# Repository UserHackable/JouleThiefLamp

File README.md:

## Steam Punk Joule Thief Flashlight Project

This is another one of my Cache Makers 4H projects. 

We used a ferrite core to wind a small transformer, an LED, a 2N3904 Transistor and a resistor to make a tiny boost circuit regulated only by the knee voltage of the LED. 

I designed the circuit board to be snapped in half, and sandwich the transformer. The whole thing was then put into a 1/2 inch copper pipe union, with a couple inches of copper pipe and a cap for a case. 

## JouleThiefLamp 

### Board dimensions

* (119996, 60000) original units
* (1.2000, 0.6000) inches
* (30.4790, 15.2400) mm

| Front | Back |
| --- | --- |
|  |  |

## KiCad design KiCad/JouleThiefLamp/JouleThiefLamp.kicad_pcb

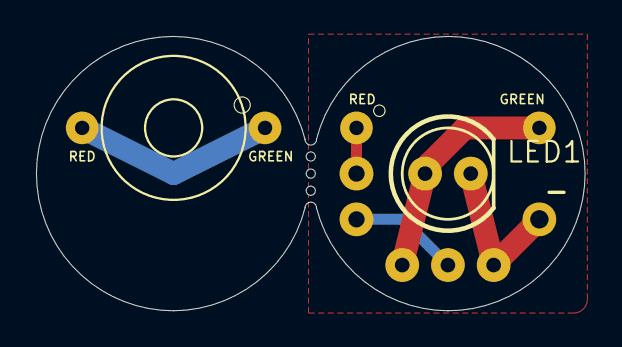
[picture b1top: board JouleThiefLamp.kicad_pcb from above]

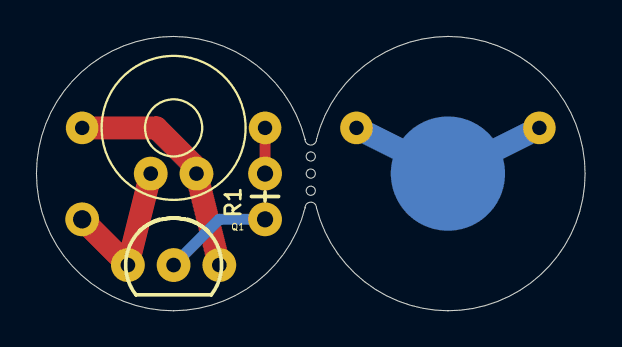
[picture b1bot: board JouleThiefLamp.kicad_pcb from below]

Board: 2 copper layers, 30.5 x 15.2 mm, 10 parts (4 on the bottom side), 5 nets.

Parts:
JP1: M01SMDNS; 1X01NS
LED1: LED5MM
Q1: TO-92-AMMO
R1: AXIAL-0.1
U$1: AA+BATT; AA+
U$2, U$3: HALF_CHOKE
UNK_HOLE_0: dummyfp0
UNK_HOLE_1: dummyfp1
UNK_HOLE_2: dummyfp2

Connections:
-: JP1.1, LED1.K, Q1.1
unnamed: R1.P$2, U$3.OUTSIDE
unnamed: LED1.A, Q1.3, U$3.CENTER
unnamed: Q1.2, R1.P$1
V_BATT: U$1.BATT+, U$2.CENTER, U$2.OUTSIDE

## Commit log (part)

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2016-04-08 from Makefile
